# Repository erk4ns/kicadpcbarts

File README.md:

# kicadpcbarts
These are the pcb files from my project for the PCBarts course. The backlight project is a pcb with leds. It is planned to be used as a backlight for the frontdesign pcb. I want to solder the powercords from an USB-cable to the backlight pcb so i can save space and dont need a plug.

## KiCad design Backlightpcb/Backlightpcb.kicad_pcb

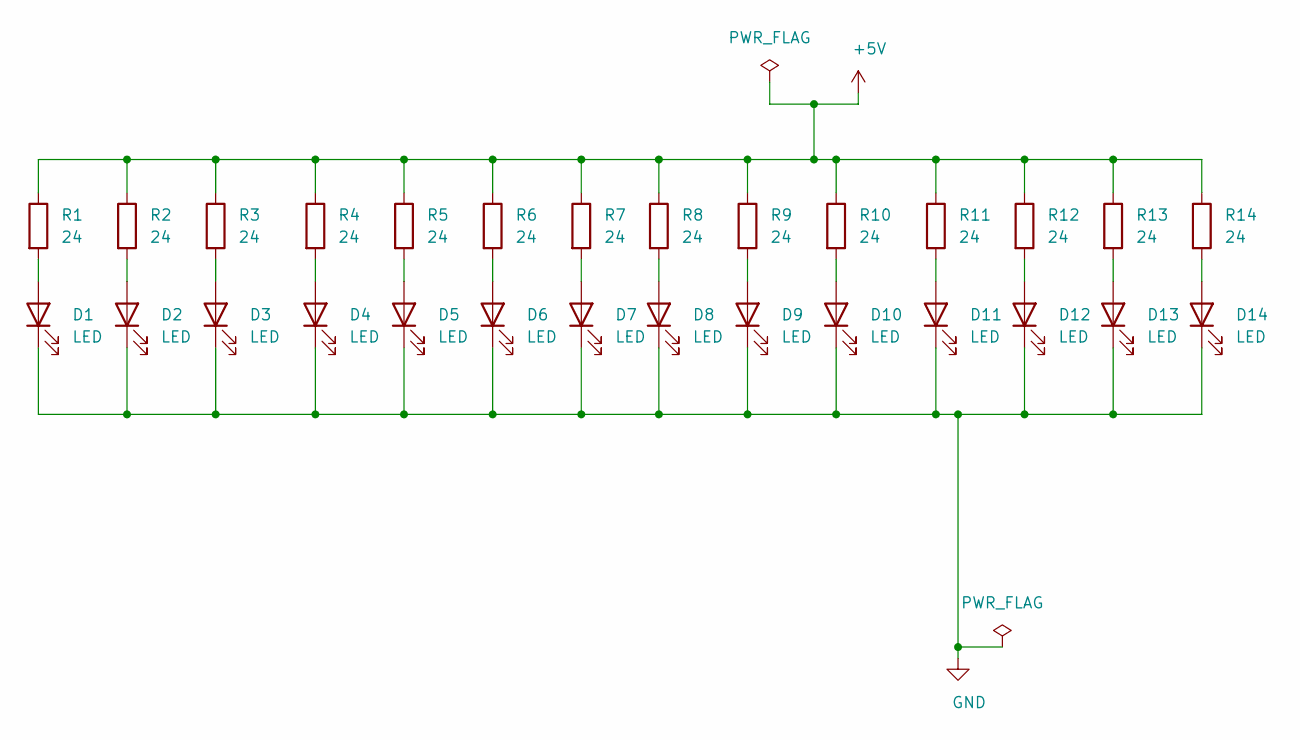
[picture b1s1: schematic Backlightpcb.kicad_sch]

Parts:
D1, D2, D3, D4, D5, D6, D7, D8, D9, D10, D11, D12, D13, D14: LED; LED_D5.0mm_Clear
R1, R2, R3, R4, R5, R6, R7, R8, R9, R10, R11, R12, R13, R14: 24; R_Axial_DIN0204_L3.6mm_D1.6mm_P5.08mm_Vertical

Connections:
+5V: R1.1, R2.1, R3.1, R4.1, R5.1, R6.1, R7.1, R8.1, R9.1, R10.1, R11.1, R12.1, R13.1, R14.1; also elsewhere on the board
GND: D1.1 (K), D2.1 (K), D3.1 (K), D4.1 (K), D5.1 (K), D6.1 (K), D7.1 (K), D8.1 (K), D9.1 (K), D10.1 (K), D11.1 (K), D12.1 (K), D13.1 (K), D14.1 (K); also elsewhere on the board
unnamed: D1.2 (A), R1.2
unnamed: D2.2 (A), R2.2
unnamed: D3.2 (A), R3.2
unnamed: D4.2 (A), R4.2
unnamed: D5.2 (A), R5.2
unnamed: D6.2 (A), R6.2
unnamed: D7.2 (A), R7.2
unnamed: D8.2 (A), R8.2
unnamed: D9.2 (A), R9.2
unnamed: D10.2 (A), R10.2
unnamed: D11.2 (A), R11.2
unnamed: D12.2 (A), R12.2
unnamed: D13.2 (A), R13.2
unnamed: D14.2 (A), R14.2

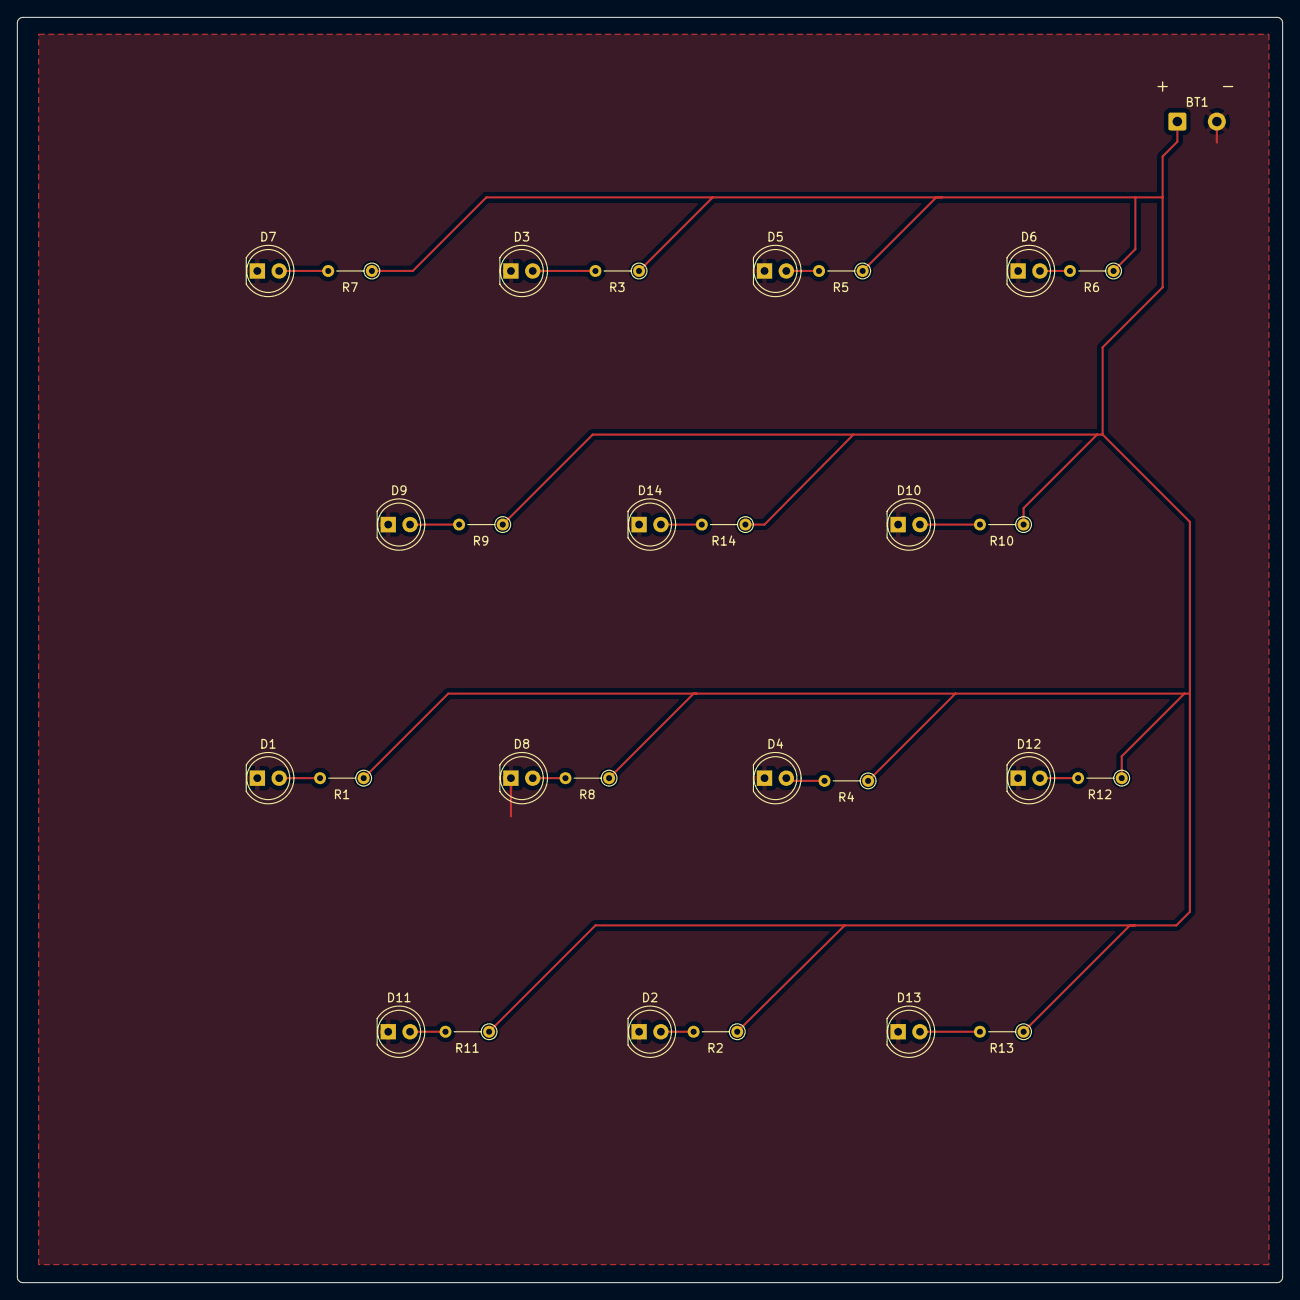
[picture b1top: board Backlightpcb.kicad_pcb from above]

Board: 2 copper layers, 147.3 x 147.3 mm, 29 parts (0 on the bottom side), 16 nets.

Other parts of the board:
BT1: Battery_Cell; SolderWire-0.5sqmm_1x02_P4.6mm_D0.9mm_OD2.1mm

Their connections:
+5V: BT1.1 (+); also elsewhere on the board
GND: BT1.2 (-); also elsewhere on the board

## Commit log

2021-01-11 The pcb files from my PCBarts course project
2021-01-11 test
2021-01-11 with files not deleted?
2021-01-11 files renamed
2021-01-17 put the files into seperated projects, added scheme for backplate, changed design of frontplate, added rounded corners to both and changed the backplate pcbdesign
2021-01-17 changed readme
2021-01-18 GND Zone
2021-01-24 changes in frontdesign
